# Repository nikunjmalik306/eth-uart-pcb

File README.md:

# ETH-UART PCB

An STM32-based Ethernet-to-UART development board designed in Autodesk EAGLE.

The board combines an STM32F407VE microcontroller with a DP83848 Ethernet PHY, RJ45 Ethernet interface, USB connectivity, multiple UART interfaces, SWD programming/debug access, status LEDs, test points, and selectable configuration jumpers.

## Features

- **MCU:** STM32F407VE
- **Ethernet PHY:** TI DP83848
- **Ethernet connector:** RJ45 with integrated magnetics
- **USB:** Micro-B connector
- **UART:** UART1, UART2, UART3 and UART5 signals
- **Debug/programming:** SWDIO and SWCLK
- **Clocks:** 8 MHz MCU oscillator and 25 MHz Ethernet PHY oscillator
- **Power:** 5 V input with 3.3 V regulation
- **Indicators:** Ethernet/activity/status LEDs
- **Test access:** IO and CLK test points
- **PCB size:** approximately **52 mm × 21 mm**
- **Design tool:** Autodesk EAGLE 9.6.2

## Repository Contents

```text
.
├── README.md
├── LICENSE
├── eth-uart.sch              # EAGLE schematic
├── eth-uart.brd              # EAGLE PCB layout
├── eagle.epf                 # EAGLE project file
└── doc/
    ├── img/
    │   ├── pcb_top.png
    │   └── pcb_bottom.png
    └── gerber/
        ├── copper_top.gbr
        ├── copper_bottom.gbr
        ├── soldermask_top.gbr
        ├── soldermask_bottom.gbr
        ├── silkscreen_top.gbr
        ├── silkscreen_bottom.gbr
        ├── profile.gbr
        ├── drills.xln
        └── project.gvp
```

## PCB Preview

### Top

### Bottom

## Main Interfaces

| Interface | Signals |
|---|---|
| Ethernet | TXDP, TXDM, RXDP, RXDM |
| Ethernet MAC | ETH_TXD0–ETH_TXD3, ETH_RXD0–ETH_RXD3, ETH_TX_EN, ETH_RX_DV, ETH_RX_CLK, ETH_TX_CLK, ETH_CRS, ETH_COL, ETH_MDC, ETH_MDIO |
| UART | UART1_TX/RX, UART2_TX/RX, UART3_TX/RX, UART5_TX/RX |
| USB FS | USB_FS_DP, USB_FS_DM |
| Debug | SWD_IO, SWD_CLK |
| Boot | BOOT0 |
| Clock | SYS_CLK, PHY_OSC |

## Opening the Design

Open the project with **Autodesk EAGLE 9.x** or a compatible version.

1. Open `eagle.epf`.
2. Open `eth-uart.sch` to inspect the schematic.
3. Open `eth-uart.brd` to inspect or modify the PCB layout.
4. Review the design rules, libraries, footprints, and component availability before manufacturing.

## Manufacturing

The `doc/gerber/` directory contains generated manufacturing files.

Before sending the files to a PCB manufacturer, verify:

- board outline/profile
- copper layers
- solder-mask layers
- silkscreen layers
- drill file
- fabrication tolerances and stack-up
- component footprints
- assembly requirements

> **Important:** This is an open hardware design. Always verify the schematic, PCB layout, component ratings, footprints, and manufacturing files before building or ordering hardware.

## Credits

**Project maintainer:** **Nikunj Malik**

GitHub: [@nikunjmalik306](https://github.com/nikunjmalik306)

The repository is maintained and published by Nikunj Malik under the MIT License.

## License

This project is licensed under the **MIT License**. See [`LICENSE`](LICENSE) for the complete license text.

SPDX-License-Identifier: MIT

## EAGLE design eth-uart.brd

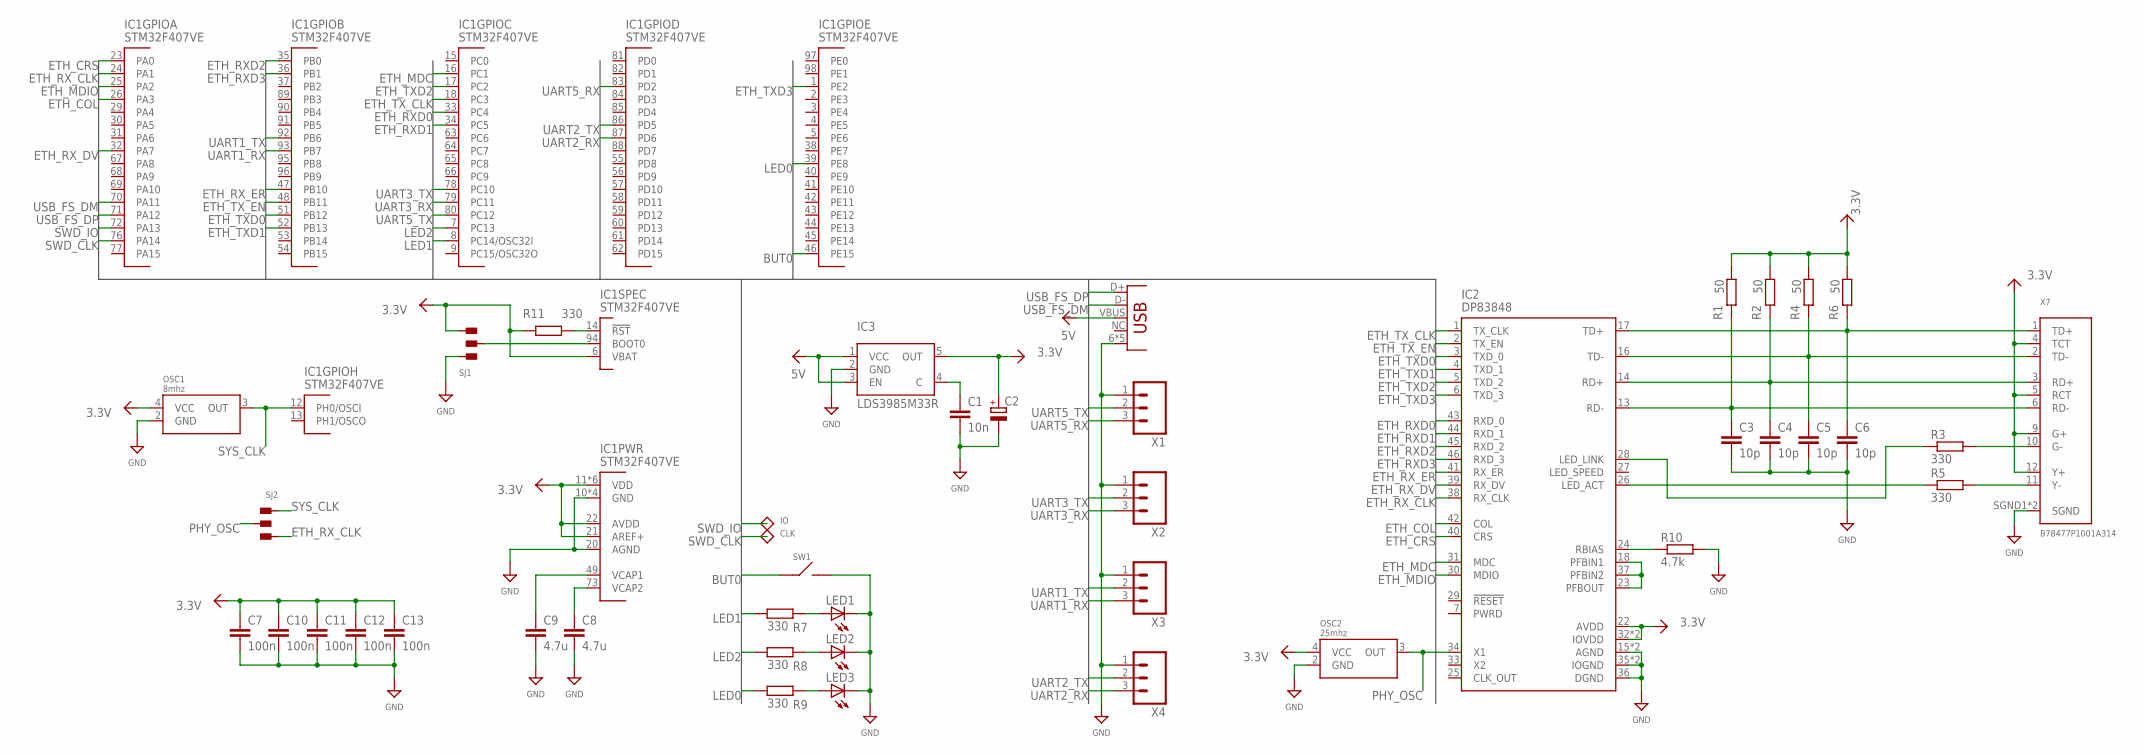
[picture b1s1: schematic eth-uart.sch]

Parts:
C1: 10n; R0402
C2: CPOL-EUSMCA; SMC_A
C3, C4, C5, C6: 10p; R0402
C7, C10, C11, C12, C13: 100n; R0402
C8, C9: 4.7u; R0603
IC1: STM32F407VE; LQFP100
IC2: DP83848; LQFP-48
IC3: LDS3985M33R; SOT23-5
LED1, LED2, LED3: LED0603
OSC1: 8mhz; 3225
OSC2: 25mhz; 3225
R1, R2, R4, R6: 50; R0402
R3, R5, R7, R8, R9, R11: 330; R0402
R10: 4.7k; R0402
SJ1, SJ2: SJ3
SW1: BUT; SONY_ERRICSON_SW
TP1: IO; TP06R
TP2: CLK; TP06R
X1, X2, X3, X4: M03; 1X03
X5: USBMICRO_B; USB_MICROB
X7: B78477P1001A314; HR911105A

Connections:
3.3V: C2.+, C7.1, C10.1, C11.1, C12.1, C13.1, IC1.6 (VBAT), IC1.11 (VDD), IC1.19 (VDD), IC1.21 (AREF+), IC1.22 (AVDD), IC1.28 (VDD), IC1.50 (VDD), IC1.75 (VDD), IC1.100 (VDD), IC2.22 (AVDD), IC2.32 (IOVDD), IC2.48 (IOVDD), IC3.5 (OUT), OSC1.4 (VCC), OSC2.4 (VCC), R1.1, R2.1, R4.1, R6.1, R11.1, SJ1.3, X7.4 (TCT), X7.5 (RCT), X7.9 (G+), X7.12 (Y+)
5V: IC3.1 (VCC), IC3.3 (EN), X5.VBUS
BOOT0: IC1.94 (BOOT0), SJ1.2
BUT0: IC1.46 (PE15), SW1.1
ETH_COL: IC1.26 (PA3), IC2.42 (COL)
ETH_CRS: IC1.23 (PA0), IC2.40 (CRS)
ETH_MDC: IC1.16 (PC1), IC2.31 (MDC)
ETH_MDIO: IC1.25 (PA2), IC2.30 (MDIO)
ETH_RXD0: IC1.33 (PC4), IC2.43 (RXD_0)
ETH_RXD1: IC1.34 (PC5), IC2.44 (RXD_1)
ETH_RXD2: IC1.35 (PB0), IC2.45 (RXD_2)
ETH_RXD3: IC1.36 (PB1), IC2.46 (RXD_3)
ETH_RX_CLK: IC1.24 (PA1), IC2.38 (RX_CLK), SJ2.3
ETH_RX_DV: IC1.32 (PA7), IC2.39 (RX_DV)
ETH_RX_ER: IC1.47 (PB10), IC2.41 (RX_ER)
ETH_TXD0: IC1.51 (PB12), IC2.3 (TXD_0)
ETH_TXD1: IC1.52 (PB13), IC2.4 (TXD_1)
ETH_TXD2: IC1.17 (PC2), IC2.5 (TXD_2)
ETH_TXD3: IC1.1 (PE2), IC2.6 (TXD_3)
ETH_TX_CLK: IC1.18 (PC3), IC2.1 (TX_CLK)
ETH_TX_EN: IC1.48 (PB11), IC2.2 (TX_EN)
GND: C1.2, C2.-, C3.2, C4.2, C5.2, C6.2, C7.2, C8.2, C9.2, C10.2, C11.2, C12.2, C13.2, IC1.10 (GND), IC1.20 (AGND), IC1.27 (GND), IC1.74 (GND), IC1.99 (GND), IC2.15 (AGND), IC2.19 (AGND), IC2.35 (IOGND), IC2.36 (DGND), IC2.47 (IOGND), IC3.2 (GND), LED1.C, LED2.C, LED3.C, OSC1.2 (GND), OSC2.2 (GND), R10.2, SJ1.1, SW1.2, X1.1, X2.1, X3.1, X4.1, X5.6 (GND), X5.7 (GND), X5.8 (GND), X5.9 (GND), X5.GND, X7.SGND1 (SGND), X7.SGND2 (SGND)
LED0: IC1.39 (PE8), R9.1
LED1: IC1.8 (PC14/OSC32I), R7.1
LED2: IC1.7 (PC13), R8.1
LED_ACT: IC2.26 (LED_ACT), R5.1
LED_G: R3.2, X7.10 (G-)
LED_LINK: IC2.28 (LED_LINK), R3.1
LED_Y: R5.2, X7.11 (Y-)
unnamed: IC1.14 (!RST), R11.2
unnamed: IC2.18 (PFBIN1), IC2.23 (PFBOUT), IC2.37 (PFBIN2)
unnamed: C1.1, IC3.4 (C)
unnamed: LED1.A, R7.2
unnamed: LED2.A, R8.2
unnamed: LED3.A, R9.2
unnamed: IC2.24 (RBIAS), R10.1
unnamed: C8.1, IC1.73 (VCAP2)
unnamed: C9.1, IC1.49 (VCAP1)
PHY_OSC: IC2.34 (X1), OSC2.3 (OUT), SJ2.2
RXDM: C3.1, IC2.13 (RD-), R1.2, X7.6 (RD-)
RXDP: C4.1, IC2.14 (RD+), R2.2, X7.3 (RD+)
SWD_CLK: IC1.76 (PA14), TP2.TP
SWD_IO: IC1.72 (PA13), TP1.TP
SYS_CLK: IC1.12 (PH0/OSCI), OSC1.3 (OUT), SJ2.1
TXDM: C5.1, IC2.16 (TD-), R4.2, X7.2 (TD-)
TXDP: C6.1, IC2.17 (TD+), R6.2, X7.1 (TD+)
UART1_RX: IC1.93 (PB7), X3.3
UART1_TX: IC1.92 (PB6), X3.2
UART2_RX: IC1.87 (PD6), X4.3
UART2_TX: IC1.86 (PD5), X4.2
UART3_RX: IC1.79 (PC11), X2.3
UART3_TX: IC1.78 (PC10), X2.2
UART5_RX: IC1.83 (PD2), X1.3
UART5_TX: IC1.80 (PC12), X1.2
USB_FS_DM: IC1.70 (PA11), X5.D-
USB_FS_DP: IC1.71 (PA12), X5.D+

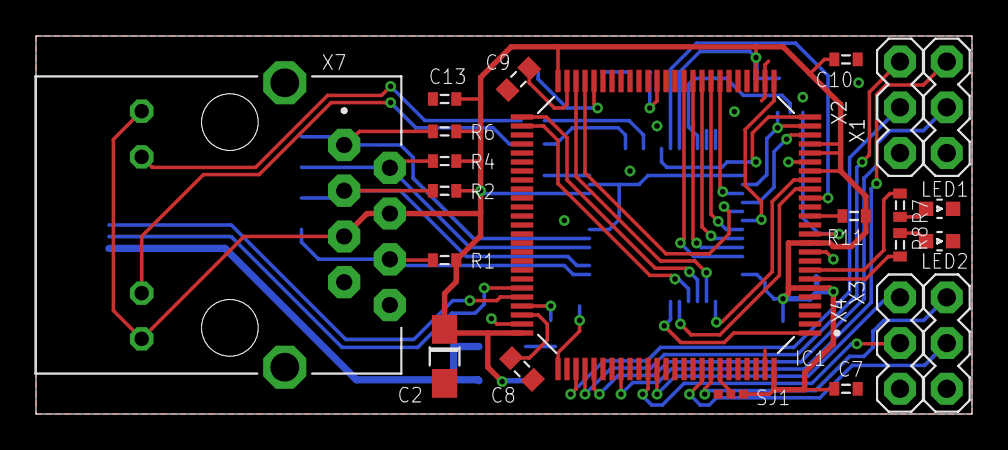
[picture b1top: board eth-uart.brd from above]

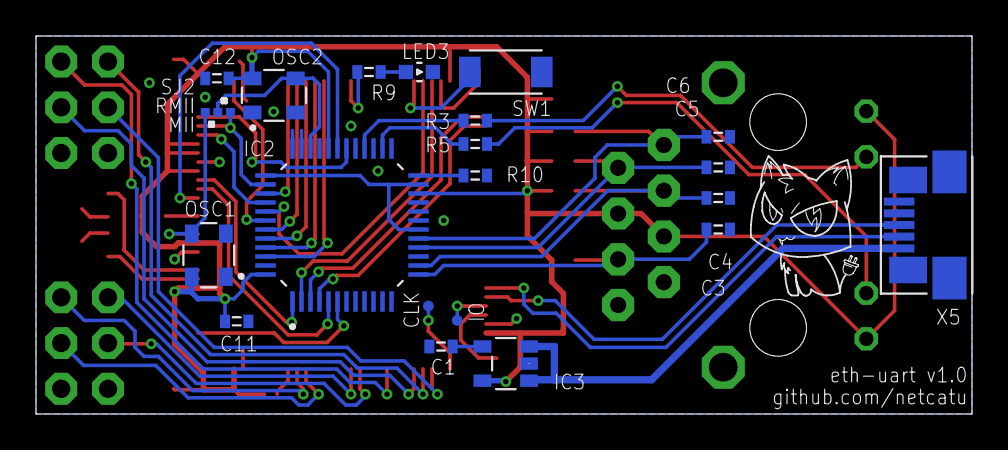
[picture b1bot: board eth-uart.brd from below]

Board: 2 copper layers, 52.0 x 21.0 mm, 44 parts (22 on the bottom side), 56 nets.

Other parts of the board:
U$1: LOGO2
